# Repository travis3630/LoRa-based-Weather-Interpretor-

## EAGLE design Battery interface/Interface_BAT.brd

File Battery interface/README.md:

Battery Interface Circuit Board
==============================
-A battery and Intereface Circuit is design for the arduino such that the board can
 directly plug onto the pins of the Arduino and it will power up the Arduino through Battery.

 Features
--------
- Plug onto arduino, on top of dragino LoRa shield, transmitter.
- Contains Battery Charger which charger up the battery through MicroUSB port.
- Charger output is regulated to 5V by MAX1796 chip.
- Interface circuit contains TEMT6000(Light detector) and DHT22 with pull down resistors.

Connections
-----------
-Battery Interface - Dragino LoRA Shield - Arduino

-DHT22 Signal - Digital IO Pin2

-TEMT6000 - Analog 0

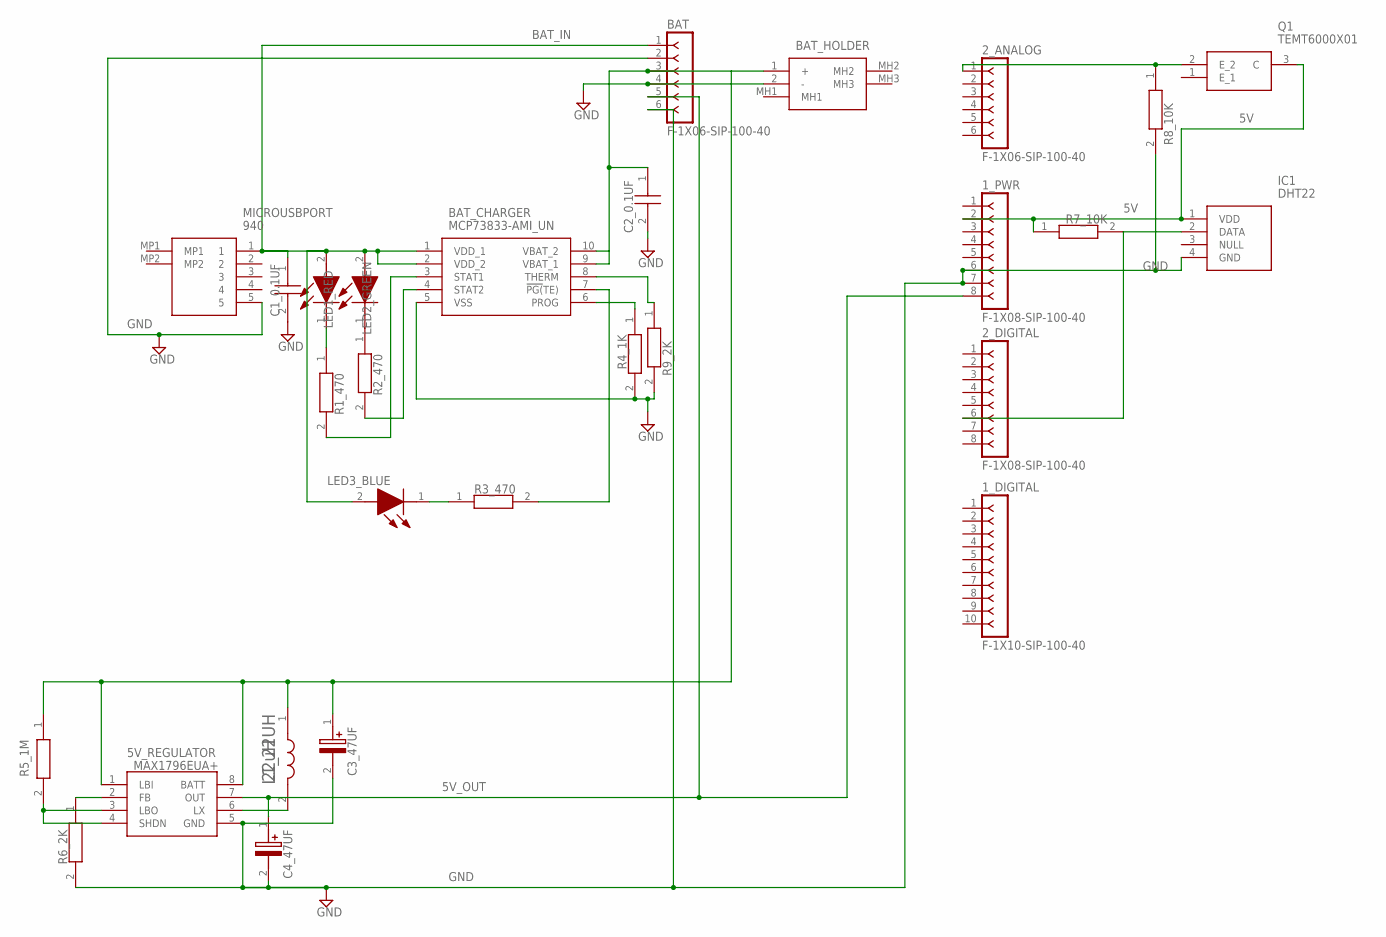
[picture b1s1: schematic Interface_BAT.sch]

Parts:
1_DIGITAL: F-1X10-SIP-100-40; SIP-100-10-40
1_PWR, 2_DIGITAL: F-1X08-SIP-100-40; SIP-100-08-40
2_ANALOG: F-1X06-SIP-100-40; SIP-100-06-40
5V_REGULATOR: MAX1796EUA+; SOP65P490X110-8N
BAT: F-1X06-SIP-100-40; SIP-100-06-40
BAT_CHARGER: MCP73833-AMI_UN; SOP50P490X110-10N
BAT_HOLDER: 1043
C1_0.1UF, C2_0.1UF: C0805C104J5RACTU; CAPC2012X88N
C3_47UF, C4_47UF: 10TPB47M; CAPPM3528X210N
IC1: DHT22
L1_22UH: COILCRAFT_LPS4018-223MRBCOILCRAFT_LPS4018-223MRB_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; COILCRAFT_LPS4018-223MRB_0
LED1_RED, LED2_GREEN, LED3_BLUE: KP-2012CGCK; LEDC2012X110N
MICROUSBPORT: 940
Q1: TEMT6000X01
R1_470, R2_470, R3_470: CRCW0805470RFKEA; RESC2012X50N
R4_1K: CRCW08051K00FKEA; RESC2012X50N
R5_1M: ERA6AEB105V; RESC2012X60N
R6_2K, R9_2K: CRCW08052K00FKEA; RESC2012X50N
R7_10K, R8_10K: ERJ6GEYJ103V; RESC2012X70N

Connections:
5V: 1_PWR.2, IC1.1 (VDD), Q1.3 (C), R7_10K.1
5V_OUT: 1_PWR.8, 5V_REGULATOR.7 (OUT), BAT.5, C4_47UF.1 (+)
BAT_IN: BAT.1, BAT_CHARGER.1 (VDD_1), BAT_CHARGER.2 (VDD_2), C1_0.1UF.1, LED1_RED.2 (A), LED2_GREEN.2 (A), LED3_BLUE.2 (A), MICROUSBPORT.1
GND: 1_PWR.6, 1_PWR.7, 5V_REGULATOR.5 (GND), BAT.2, BAT.4, BAT.6, BAT_CHARGER.5 (VSS), BAT_HOLDER.2 (-), C1_0.1UF.2, C2_0.1UF.2, C3_47UF.2 (-), C4_47UF.2 (-), IC1.4 (GND), MICROUSBPORT.5, R4_1K.2, R6_2K.2, R8_10K.2, R9_2K.2
unnamed: 5V_REGULATOR.1 (LBI), 5V_REGULATOR.8 (BATT), BAT.3, BAT_CHARGER.9 (VBAT_1), BAT_CHARGER.10 (VBAT_2), BAT_HOLDER.1 (+), C2_0.1UF.1, C3_47UF.1 (+), L1_22UH.1, R5_1M.1
unnamed: LED1_RED.1 (K), R1_470.1
unnamed: LED2_GREEN.1 (K), R2_470.1
unnamed: BAT_CHARGER.7 (!PG(!TE)), R3_470.2
unnamed: BAT_CHARGER.4 (STAT2), R2_470.2
unnamed: BAT_CHARGER.6 (PROG), R4_1K.1
unnamed: BAT_CHARGER.3 (STAT1), R1_470.2
unnamed: LED3_BLUE.1 (K), R3_470.1
unnamed: 5V_REGULATOR.3 (LBO), 5V_REGULATOR.4 (SHDN), R5_1M.2
unnamed: BAT_CHARGER.8 (THERM), R9_2K.1
unnamed: 5V_REGULATOR.2 (FB), R6_2K.1
unnamed: 5V_REGULATOR.6 (LX), L1_22UH.2
unnamed: 2_DIGITAL.6, IC1.2 (DATA), R7_10K.2
unnamed: 2_ANALOG.1, Q1.2 (E_2), R8_10K.1

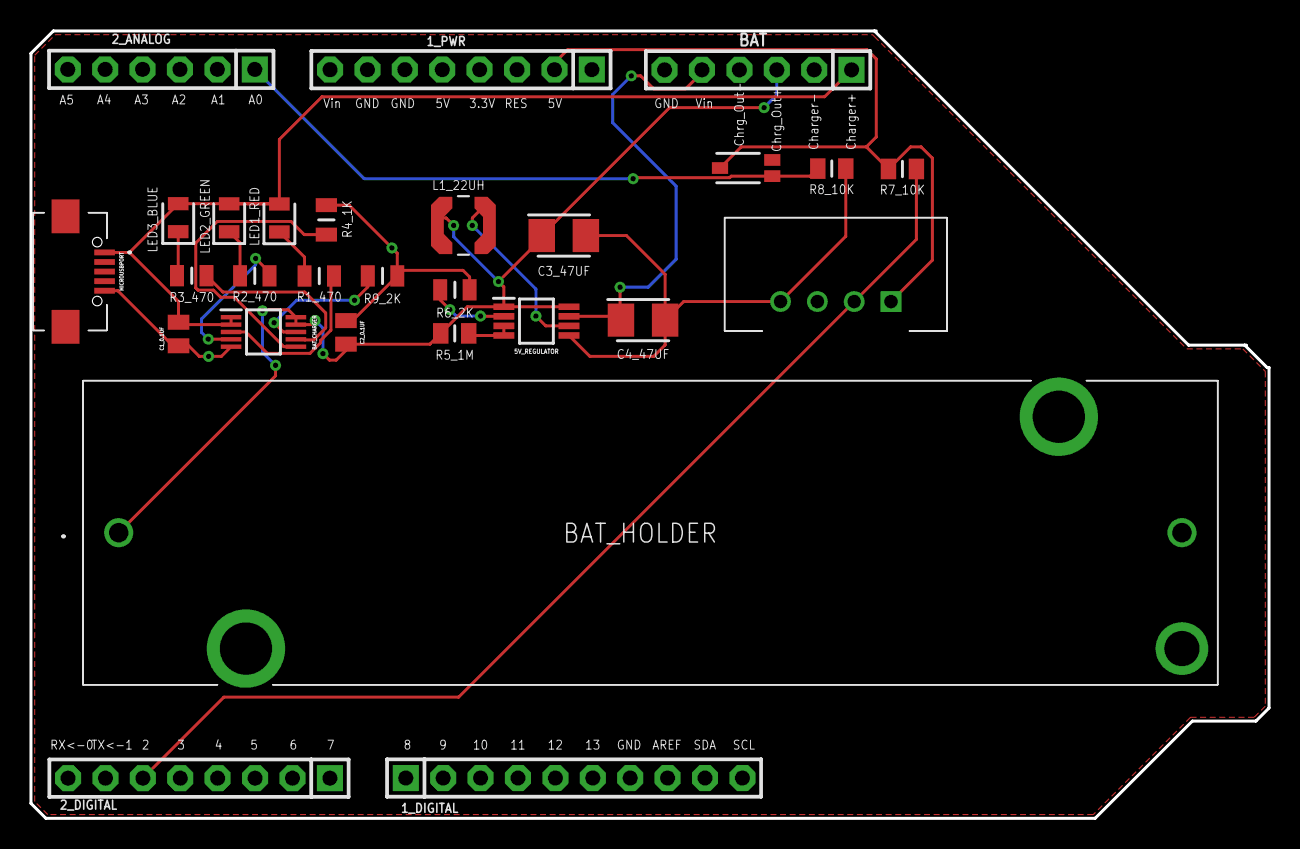
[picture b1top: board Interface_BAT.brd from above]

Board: 2 copper layers, 84.1 x 53.5 mm, 28 parts (0 on the bottom side), 18 nets.

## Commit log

2021-03-02 Create Battery Interface Design

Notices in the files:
parts and their libraries:
con-headers-jp-6pins: Copyright (C) 2008, Bob Starr
